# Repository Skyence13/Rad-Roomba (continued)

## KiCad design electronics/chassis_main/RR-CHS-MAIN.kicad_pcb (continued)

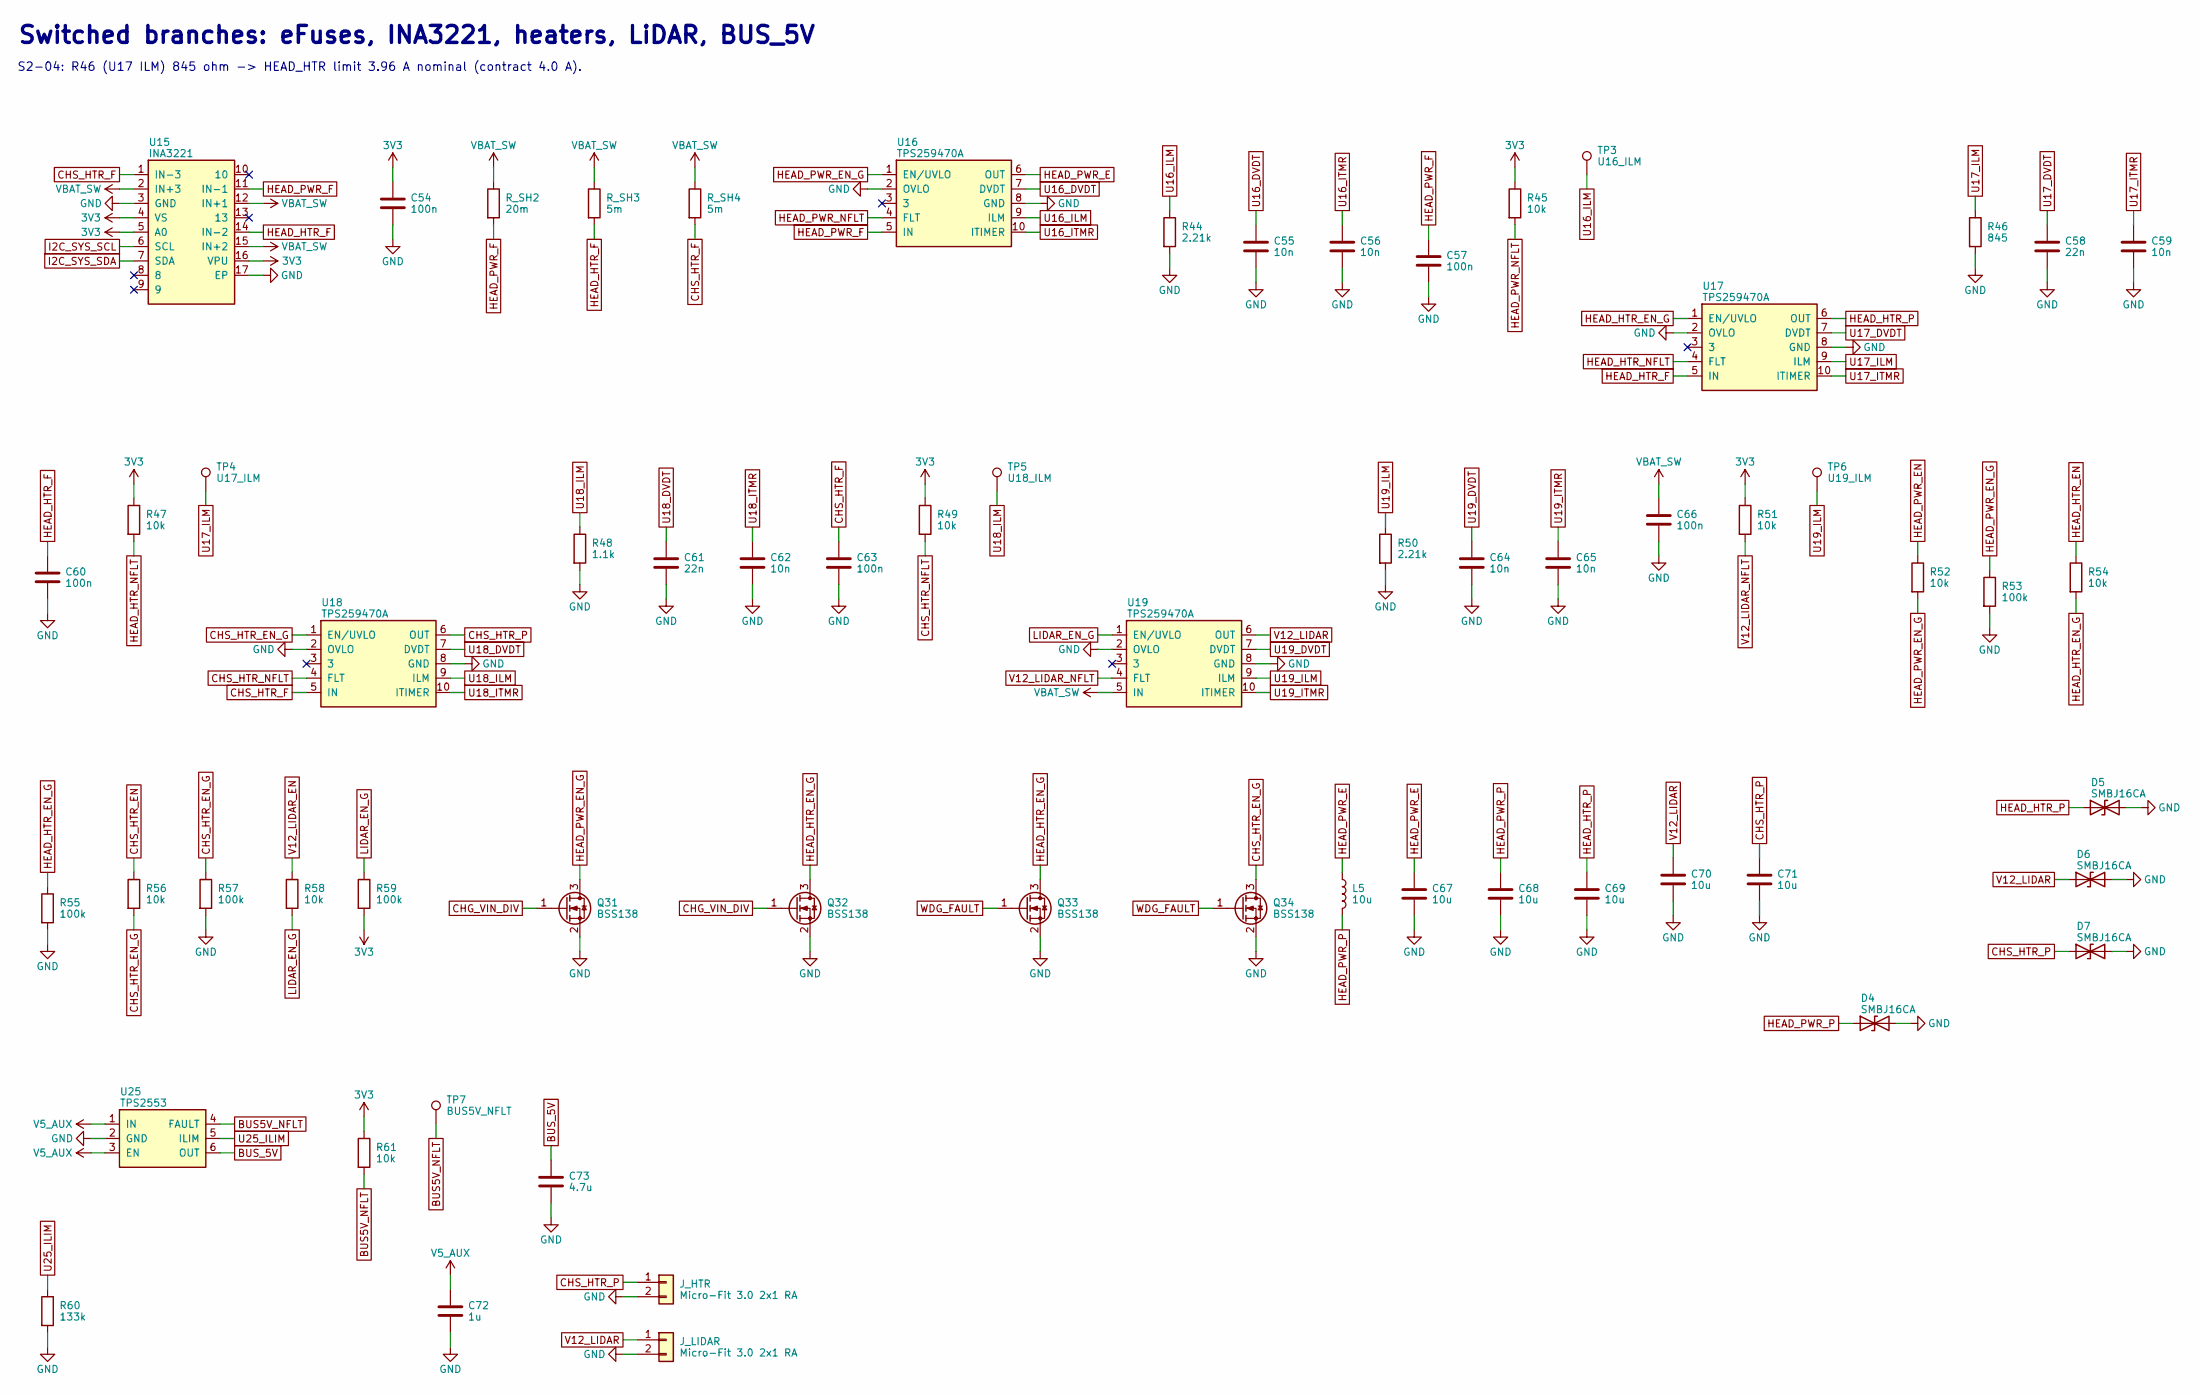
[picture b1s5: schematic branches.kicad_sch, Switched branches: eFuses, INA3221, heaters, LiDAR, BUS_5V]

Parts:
C54, C57, C60, C63, C66: 100n; C_0603_1608Metric; MPN CC0603KRX7R9BB104
C55, C56, C59, C62, C64, C65: 10n; C_0603_1608Metric; MPN CC0603KRX7R9BB103
C58, C61: 22n; C_0603_1608Metric; MPN CC0603KRX7R9BB223
C67, C68, C69, C70, C71: 10u; C_1206_3216Metric; MPN GRM31CR71E106KA12L
C72: 1u; C_0603_1608Metric; MPN GRM188R71C105KA12D
C73: 4.7u; C_0805_2012Metric; MPN GRM21BR71C475KA73L
D4, D5, D6, D7: SMBJ16CA; D_SMB; MPN SMBJ16CA
J_HTR: Micro-Fit 3.0 2x1 RA; Molex_Micro-Fit_3.0_43045-0200_2x01_P3.00mm_Horizontal; MPN 43045-0200
J_LIDAR: Micro-Fit 3.0 2x1 RA; Molex_Micro-Fit_3.0_43045-0200_2x01_P3.00mm_Horizontal; MPN 43045-0200
L5: 10u; L_Coilcraft_XAL4040-XXX; MPN XAL4040-103MEC
Q31, Q32, Q33, Q34: BSS138; SOT-23; MPN BSS138
R44, R50: 2.21k; R_0603_1608Metric; MPN RC0603FR-072K21L
R45, R47, R49, R51, R52, R54, R56, R58, R61: 10k; R_0603_1608Metric; MPN RC0603FR-0710KL
R46: 845; R_0603_1608Metric; MPN RC0603FR-07845RL
R48: 1.1k; R_0603_1608Metric; MPN RC0603FR-071K1L
R53, R55, R57, R59: 100k; R_0603_1608Metric; MPN RC0603FR-07100KL
R60: 133k; R_0603_1608Metric; MPN RC0603FR-07133KL
R_SH2: 20m; R_1206_3216Metric; MPN WSL1206R0200FEA
R_SH3, R_SH4: 5m; R_2512_6332Metric; MPN WSL25125L000FEA
TP3: U16_ILM; TestPoint_Keystone_5019_Miniature; MPN 5019
TP4: U17_ILM; TestPoint_Keystone_5019_Miniature; MPN 5019
TP5: U18_ILM; TestPoint_Keystone_5019_Miniature; MPN 5019
TP6: U19_ILM; TestPoint_Keystone_5019_Miniature; MPN 5019
TP7: BUS5V_NFLT; TestPoint_Keystone_5019_Miniature; MPN 5019
U15: INA3221; Texas_RGV0016A_VQFN-16-1EP_4x4mm_P0.65mm_EP2.1x2.1mm; MPN INA3221AIRGVR
U16, U17, U18, U19: TPS259470A; TI_RPW0010A_VQFN-HR-10_2x2mm_PLACEHOLDER; MPN TPS259470ARPWR
U25: TPS2553; SOT-23-6; MPN TPS2553DBVR

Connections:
3V3: C54.1, R45.1, R47.1, R49.1, R51.1, R59.2, R61.1, U15.4 (VS), U15.5 (A0), U15.16 (VPU); also elsewhere on the board
BUS5V_NFLT: R61.2, TP7.1, U25.4 (FAULT)
BUS_5V: C73.1, U25.6 (OUT); also elsewhere on the board
CHG_VIN_DIV: Q31.1 (G), Q32.1 (G); also elsewhere on the board
CHS_HTR_EN: R56.1; also elsewhere on the board
CHS_HTR_EN_G: Q34.3 (D), R56.2, R57.1, U18.1 (EN/UVLO)
CHS_HTR_F: C63.1, R_SH4.2, U15.1 (IN-3), U18.5 (IN)
CHS_HTR_NFLT: R49.2, U18.4 (FLT); also elsewhere on the board
CHS_HTR_P: C71.1, D7.1 (A1), J_HTR.1, U18.6 (OUT)
GND: C54.2, C55.2, C56.2, C57.2, C58.2, C59.2, C60.2, C61.2, C62.2, C63.2, C64.2, C65.2, C66.2, C67.2, C68.2, C69.2, C70.2, C71.2, C72.2, C73.2, D4.2 (A2), D5.2 (A2), D6.2 (A2), D7.2 (A2), J_HTR.2, J_LIDAR.2, Q31.2 (S), Q32.2 (S), Q33.2 (S), Q34.2 (S), R44.2, R46.2, R48.2, R50.2, R53.2, R55.2, R57.2, R60.2, U15.3 (GND), U15.17 (EP), U16.2 (OVLO), U16.8 (GND), U17.2 (OVLO), U17.8 (GND), U18.2 (OVLO), U18.8 (GND), U19.2 (OVLO), U19.8 (GND), U25.2 (GND); also elsewhere on the board
HEAD_HTR_EN: R54.1; also elsewhere on the board
HEAD_HTR_EN_G: Q32.3 (D), Q33.3 (D), R54.2, R55.1, U17.1 (EN/UVLO)
HEAD_HTR_F: C60.1, R_SH3.2, U15.14 (IN-2), U17.5 (IN)
HEAD_HTR_NFLT: R47.2, U17.4 (FLT); also elsewhere on the board
HEAD_HTR_P: C69.1, D5.1 (A1), U17.6 (OUT); also elsewhere on the board
HEAD_PWR_E: C67.1, L5.1, U16.6 (OUT)
HEAD_PWR_EN: R52.1; also elsewhere on the board
HEAD_PWR_EN_G: Q31.3 (D), R52.2, R53.1, U16.1 (EN/UVLO)
HEAD_PWR_F: C57.1, R_SH2.2, U15.11 (IN-1), U16.5 (IN)
HEAD_PWR_NFLT: R45.2, U16.4 (FLT); also elsewhere on the board
HEAD_PWR_P: C68.1, D4.1 (A1), L5.2; also elsewhere on the board
I2C_SYS_SCL: U15.6 (SCL); also elsewhere on the board
I2C_SYS_SDA: U15.7 (SDA); also elsewhere on the board
LIDAR_EN_G: R58.2, R59.1, U19.1 (EN/UVLO)
U16_DVDT: C55.1, U16.7 (DVDT)
U16_ILM: R44.1, TP3.1, U16.9 (ILM)
U16_ITMR: C56.1, U16.10 (ITIMER)
U17_DVDT: C58.1, U17.7 (DVDT)
U17_ILM: R46.1, TP4.1, U17.9 (ILM)
U17_ITMR: C59.1, U17.10 (ITIMER)
U18_DVDT: C61.1, U18.7 (DVDT)
U18_ILM: R48.1, TP5.1, U18.9 (ILM)
U18_ITMR: C62.1, U18.10 (ITIMER)
U19_DVDT: C64.1, U19.7 (DVDT)
U19_ILM: R50.1, TP6.1, U19.9 (ILM)
U19_ITMR: C65.1, U19.10 (ITIMER)
U25_ILIM: R60.1, U25.5 (ILIM)
V5_AUX: C72.1, U25.1 (IN), U25.3 (EN); also elsewhere on the board
V12_LIDAR: C70.1, D6.1 (A1), J_LIDAR.1, U19.6 (OUT)
V12_LIDAR_EN: R58.1; also elsewhere on the board
V12_LIDAR_NFLT: R51.2, U19.4 (FLT); also elsewhere on the board
VBAT_SW: C66.1, R_SH2.1, R_SH3.1, R_SH4.1, U15.2 (IN+3), U15.12 (IN+1), U15.15 (IN+2), U19.5 (IN); also elsewhere on the board
WDG_FAULT: Q33.1 (G), Q34.1 (G); also elsewhere on the board

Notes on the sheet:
Switched branches: eFuses, INA3221, heaters, LiDAR, BUS_5V
S2-04: R46 (U17 ILM) 845 ohm -> HEAD_HTR limit 3.96 A nominal (contract 4.0 A).

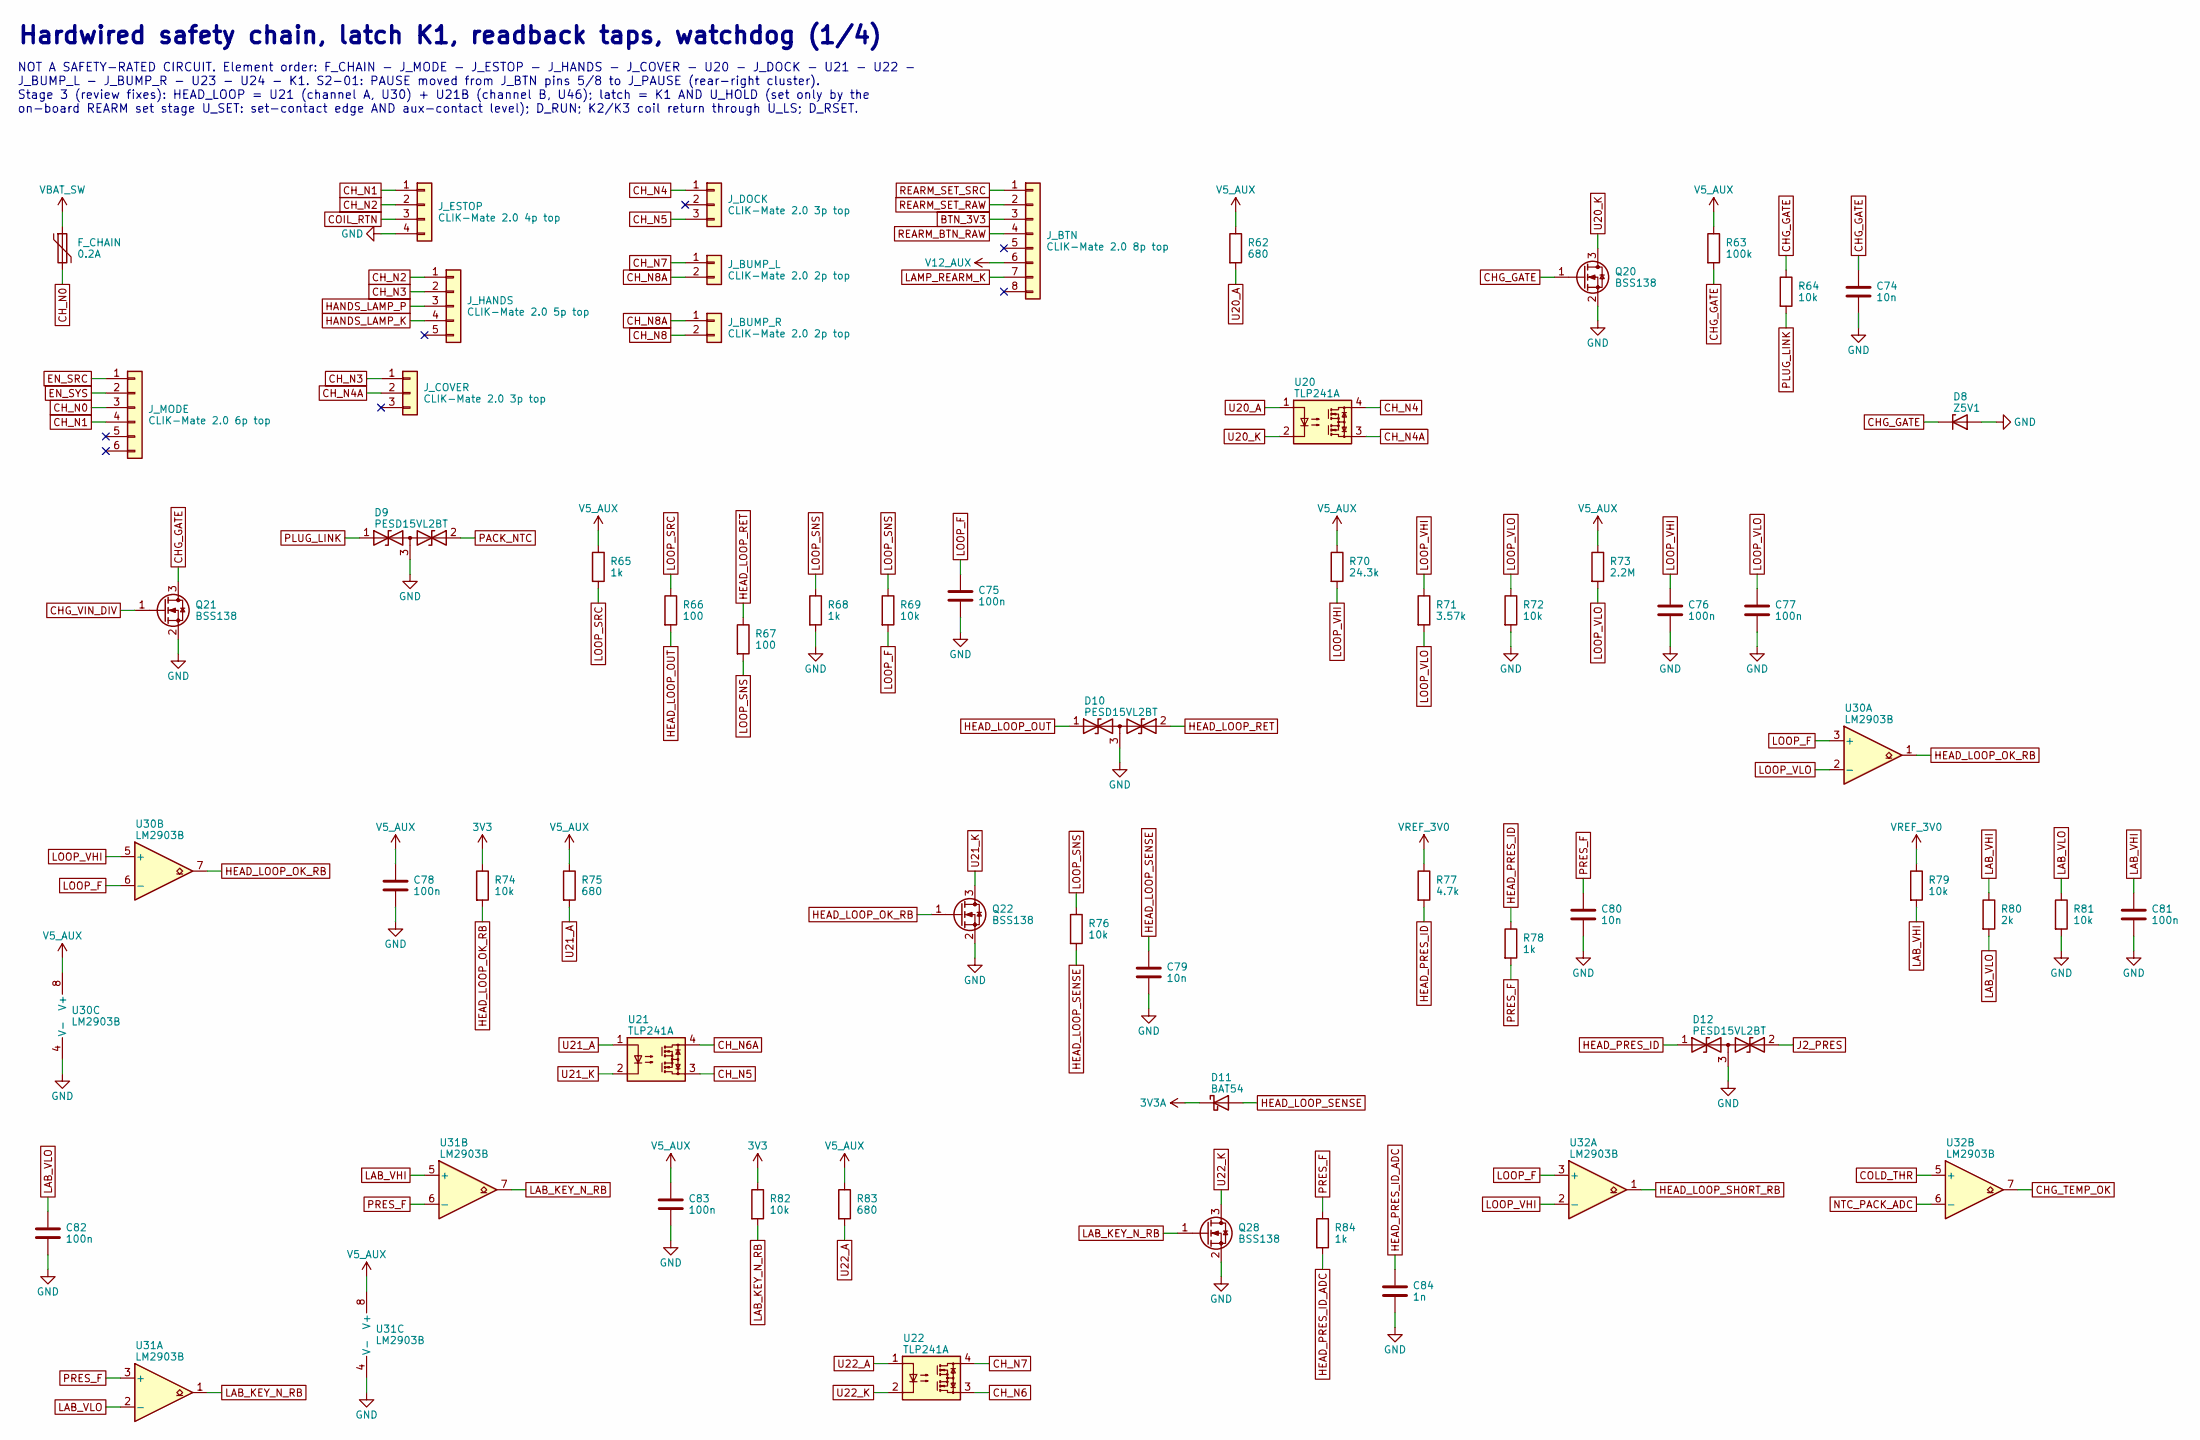
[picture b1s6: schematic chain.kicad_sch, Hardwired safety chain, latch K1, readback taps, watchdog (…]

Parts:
C74, C79, C80: 10n; C_0603_1608Metric; MPN CC0603KRX7R9BB103
C75, C76, C77, C78, C81, C82, C83: 100n; C_0603_1608Metric; MPN CC0603KRX7R9BB104
C84: 1n; C_0603_1608Metric; MPN CC0603JRNPO9BN102
D8: Z5V1; D_SOD-123; MPN BZT52C5V1-7-F
D9, D10, D12: PESD15VL2BT; SOT-23; MPN PESD15VL2BT,215
D11: BAT54; D_SOD-123; MPN BAT54W-7-F
F_CHAIN: 0.2A; Fuse_1206_3216Metric; MPN 1206L020YR
J_BTN: CLIK-Mate 2.0 8p top; Molex_CLIK-Mate_502443-0870_1x08-1MP_P2.00mm_Vertical; MPN 502443-0870
J_BUMP_L: CLIK-Mate 2.0 2p top; Molex_CLIK-Mate_502443-0270_1x02-1MP_P2.00mm_Vertical; MPN 502443-0270
J_BUMP_R: CLIK-Mate 2.0 2p top; Molex_CLIK-Mate_502443-0270_1x02-1MP_P2.00mm_Vertical; MPN 502443-0270
J_COVER: CLIK-Mate 2.0 3p top; Molex_CLIK-Mate_502443-0370_1x03-1MP_P2.00mm_Vertical; MPN 502443-0370
J_DOCK: CLIK-Mate 2.0 3p top; Molex_CLIK-Mate_502443-0370_1x03-1MP_P2.00mm_Vertical; MPN 502443-0370
J_ESTOP: CLIK-Mate 2.0 4p top; Molex_CLIK-Mate_502443-0470_1x04-1MP_P2.00mm_Vertical; MPN 502443-0470
J_HANDS: CLIK-Mate 2.0 5p top; Molex_CLIK-Mate_502443-0570_1x05-1MP_P2.00mm_Vertical; MPN 502443-0570
J_MODE: CLIK-Mate 2.0 6p top; Molex_CLIK-Mate_502443-0670_1x06-1MP_P2.00mm_Vertical; MPN 502443-0670
Q20, Q21, Q22, Q28: BSS138; SOT-23; MPN BSS138
R62, R75, R83: 680; R_0603_1608Metric; MPN RC0603FR-07680RL
R63: 100k; R_0603_1608Metric; MPN RC0603FR-07100KL
R64, R69, R74, R76, R82: 10k; R_0603_1608Metric; MPN RC0603FR-0710KL
R65, R68: 1k; R_0603_1608Metric; MPN RT0603BRD071KL
R66, R67: 100; R_0603_1608Metric; MPN RC0603FR-07100RL
R70: 24.3k; R_0603_1608Metric; MPN RT0603BRD0724K3L
R71: 3.57k; R_0603_1608Metric; MPN RT0603BRD073K57L
R72, R79, R81: 10k; R_0603_1608Metric; MPN RT0603BRD0710KL
R73: 2.2M; R_0603_1608Metric; MPN RC0603FR-072M2L
R77: 4.7k; R_0603_1608Metric; MPN RT0603BRD074K7L
R78, R84: 1k; R_0603_1608Metric; MPN RC0603FR-071KL
R80: 2k; R_0603_1608Metric; MPN RT0603BRD072KL
U20, U21, U22: TLP241A; SMDIP-4_W9.53mm; MPN TLP241A(TP1,F
U30, U31, U32: LM2903B; SOIC-8_3.9x4.9mm_P1.27mm; MPN LM2903BIDR

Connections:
3V3: R74.1, R82.1; also elsewhere on the board
3V3A: D11.1 (K); also elsewhere on the board
BTN_3V3: J_BTN.3; also elsewhere on the board
CHG_GATE: C74.1, D8.1 (K), Q20.1 (G), Q21.3 (D), R63.2, R64.1
CHG_TEMP_OK: U32.7; also elsewhere on the board
CHG_VIN_DIV: Q21.1 (G); also elsewhere on the board
CH_N0: F_CHAIN.2, J_MODE.3; also elsewhere on the board
CH_N1: J_ESTOP.1, J_MODE.4; also elsewhere on the board
CH_N2: J_ESTOP.2, J_HANDS.1; also elsewhere on the board
CH_N3: J_COVER.1, J_HANDS.2; also elsewhere on the board
CH_N4: J_DOCK.1, U20.4; also elsewhere on the board
CH_N4A: J_COVER.2, U20.3; also elsewhere on the board
CH_N5: J_DOCK.3, U21.3; also elsewhere on the board
CH_N6: U22.3; also elsewhere on the board
CH_N6A: U21.4; also elsewhere on the board
CH_N7: J_BUMP_L.1, U22.4; also elsewhere on the board
CH_N8: J_BUMP_R.2; also elsewhere on the board
CH_N8A: J_BUMP_L.2, J_BUMP_R.1; also elsewhere on the board
COIL_RTN: J_ESTOP.3; also elsewhere on the board
COLD_THR: U32.5 (+); also elsewhere on the board
EN_SRC: J_MODE.1; also elsewhere on the board
EN_SYS: J_MODE.2; also elsewhere on the board
GND: C74.2, C75.2, C76.2, C77.2, C78.2, C79.2, C80.2, C81.2, C82.2, C83.2, C84.2, D8.2 (A), D9.3 (common), D10.3 (common), D12.3 (common), J_ESTOP.4, Q20.2 (S), Q21.2 (S), Q22.2 (S), Q28.2 (S), R68.2, R72.2, R81.2, U30.4 (V-), U31.4 (V-); also elsewhere on the board
HANDS_LAMP_K: J_HANDS.4; also elsewhere on the board
HANDS_LAMP_P: J_HANDS.3; also elsewhere on the board
HEAD_LOOP_OK_RB: Q22.1 (G), R74.2, U30.1, U30.7; also elsewhere on the board
HEAD_LOOP_OUT: D10.1 (A1), R66.2; also elsewhere on the board
HEAD_LOOP_RET: D10.2 (A2), R67.1; also elsewhere on the board
HEAD_LOOP_SENSE: C79.1, D11.2 (A), R76.2; also elsewhere on the board
HEAD_LOOP_SHORT_RB: U32.1; also elsewhere on the board
HEAD_PRES_ID: D12.1 (A1), R77.2, R78.1; also elsewhere on the board
HEAD_PRES_ID_ADC: C84.1, R84.2; also elsewhere on the board
J2_PRES: D12.2 (A2); also elsewhere on the board
LAB_KEY_N_RB: Q28.1 (G), R82.2, U31.1, U31.7; also elsewhere on the board
LAB_VHI: C81.1, R79.2, R80.1, U31.5 (+)
LAB_VLO: C82.1, R80.2, R81.1, U31.2 (-)
LAMP_REARM_K: J_BTN.7; also elsewhere on the board
LOOP_F: C75.1, R69.2, U30.3 (+), U30.6 (-), U32.3 (+); also elsewhere on the board
LOOP_SNS: R67.2, R68.1, R69.1, R76.1; also elsewhere on the board
LOOP_SRC: R65.2, R66.1
LOOP_VHI: C76.1, R70.2, R71.1, U30.5 (+), U32.2 (-)
LOOP_VLO: C77.1, R71.2, R72.1, R73.2, U30.2 (-)
NTC_PACK_ADC: U32.6 (-); also elsewhere on the board
PACK_NTC: D9.2 (A2); also elsewhere on the board
PLUG_LINK: D9.1 (A1), R64.2; also elsewhere on the board
PRES_F: C80.1, R78.2, R84.1, U31.3 (+), U31.6 (-); also elsewhere on the board
REARM_BTN_RAW: J_BTN.4; also elsewhere on the board
REARM_SET_RAW: J_BTN.2; also elsewhere on the board
REARM_SET_SRC: J_BTN.1; also elsewhere on the board
U20_A: R62.2, U20.1
U20_K: Q20.3 (D), U20.2
U21_A: R75.2, U21.1
U21_K: Q22.3 (D), U21.2
U22_A: R83.2, U22.1
U22_K: Q28.3 (D), U22.2
V5_AUX: C78.1, C83.1, R62.1, R63.1, R65.1, R70.1, R73.1, R75.1, R83.1, U30.8 (V+), U31.8 (V+); also elsewhere on the board
V12_AUX: J_BTN.6; also elsewhere on the board
VBAT_SW: F_CHAIN.1; also elsewhere on the board
VREF_3V0: R77.1, R79.1; also elsewhere on the board

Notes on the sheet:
Hardwired safety chain, latch K1, readback taps, watchdog (1/4)
NOT A SAFETY-RATED CIRCUIT. Element order: F_CHAIN - J_MODE - J_ESTOP - J_HANDS - J_COVER - U20 - J_DOCK - U21 - U22 - J_BUMP_L - J_BUMP_R - U23 - U24 - K1. S2-01: PAUSE moved from J_BTN pins 5/8 to J_PAUSE (rear-right cluster). Stage 3 (review fixes): HEAD_LOOP = U21 (channel A, U30) + U21B (chann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

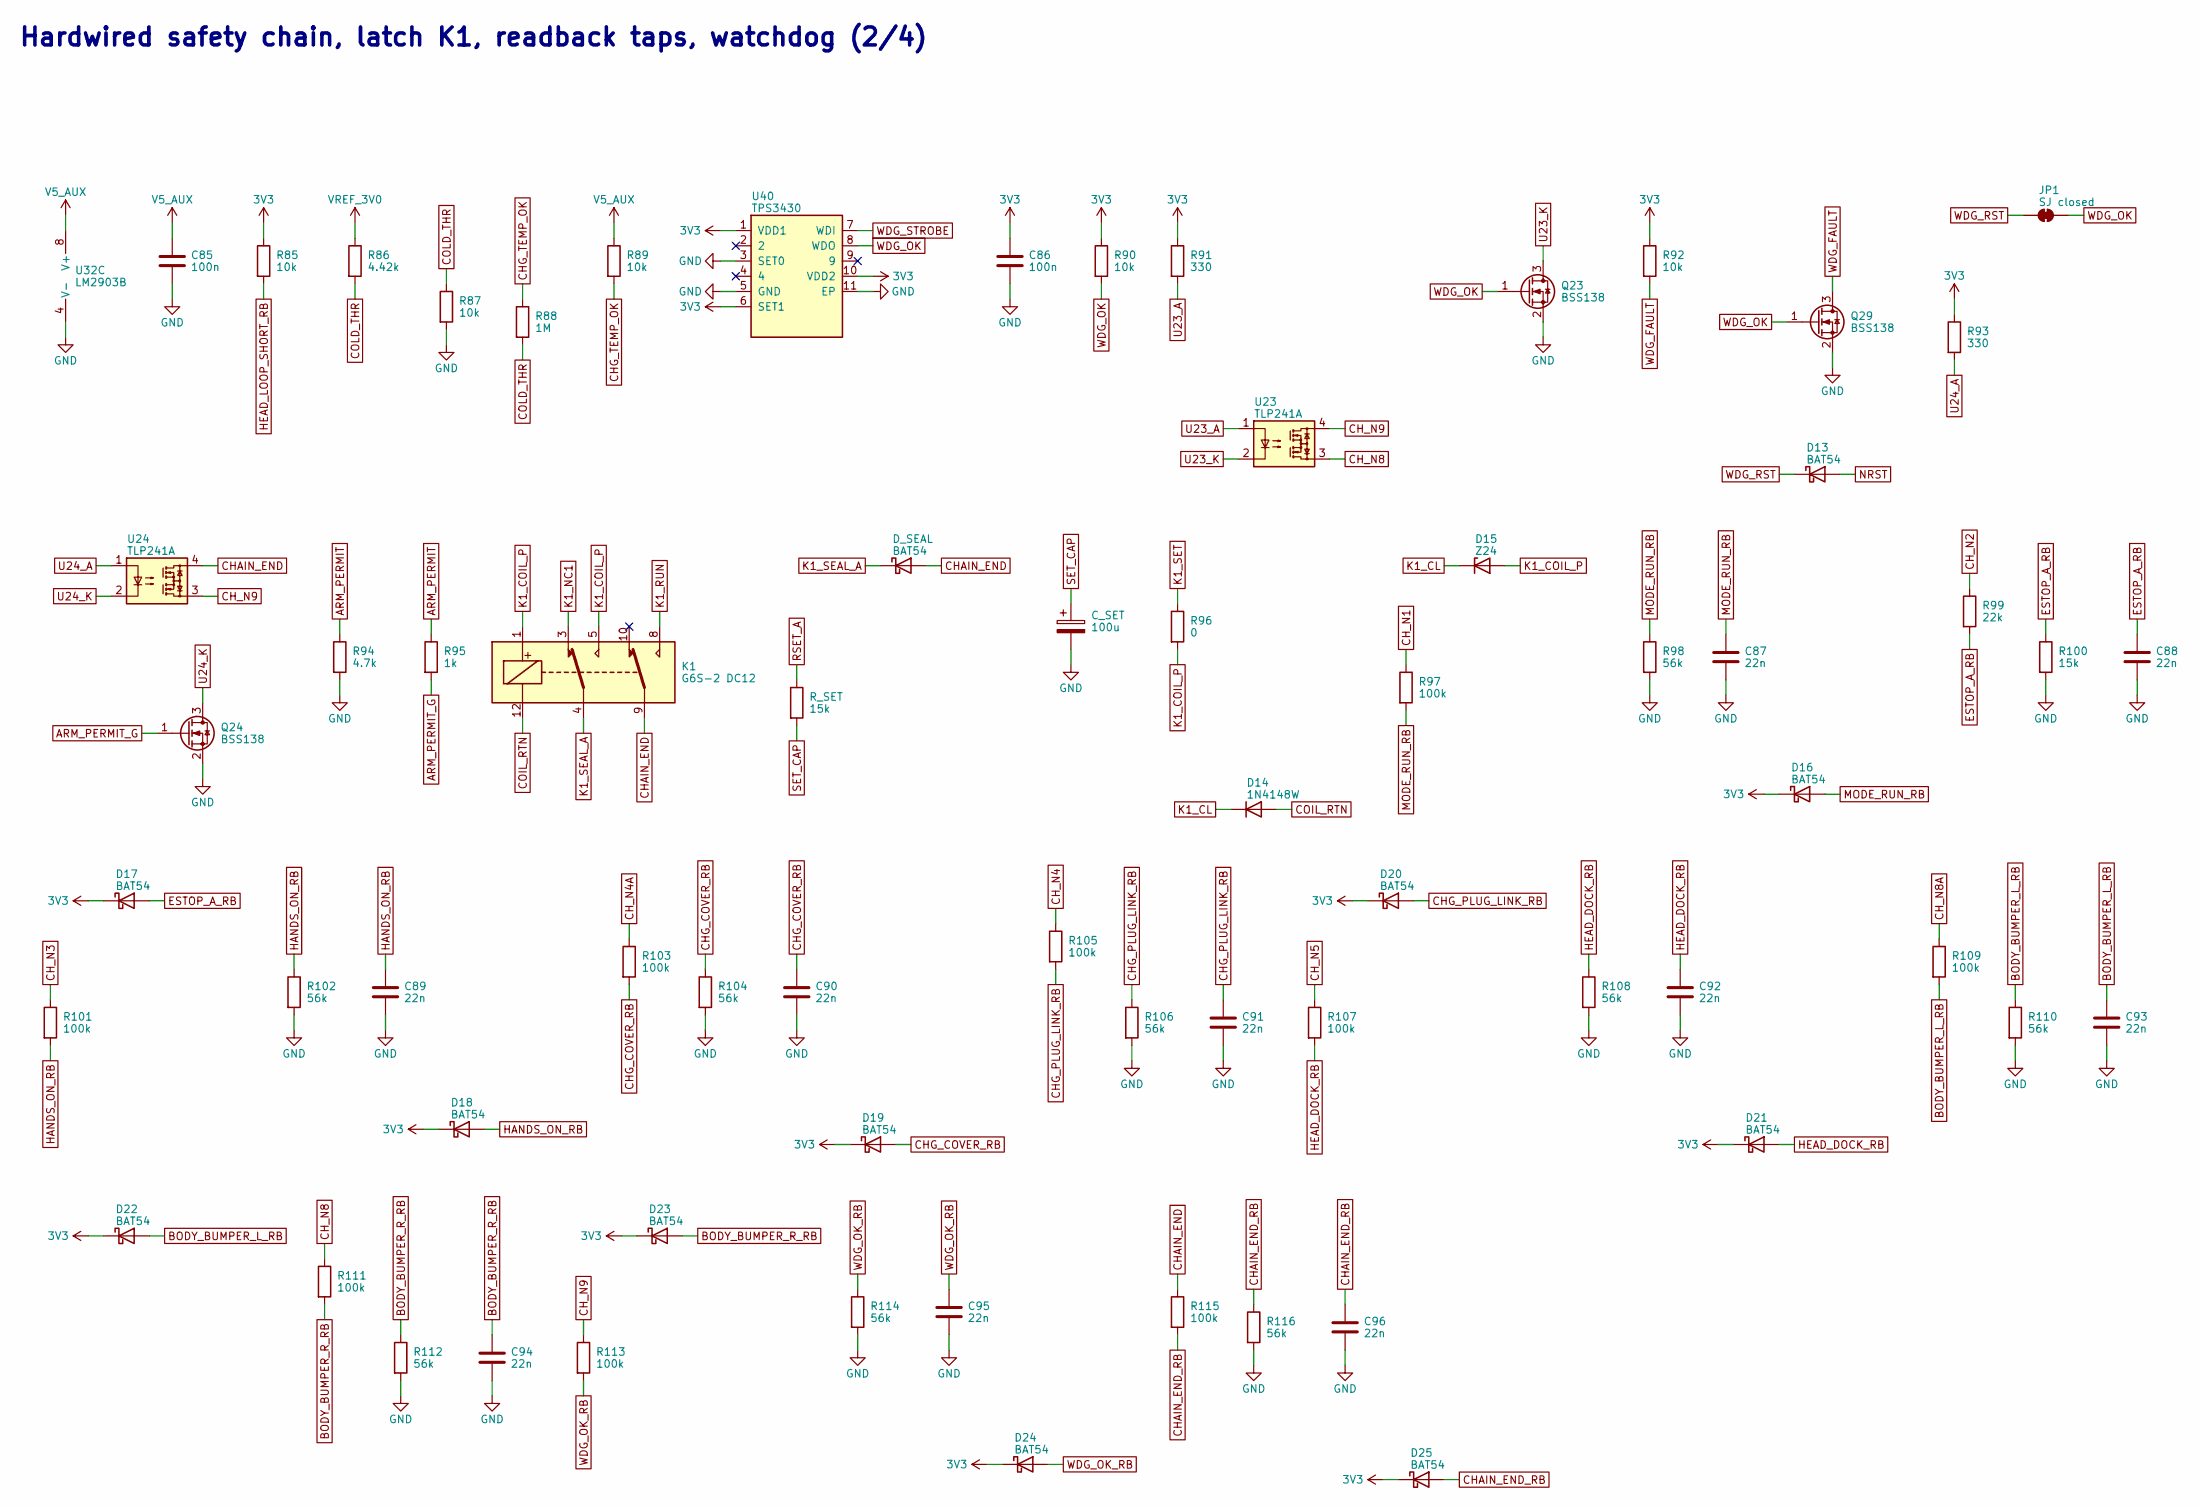
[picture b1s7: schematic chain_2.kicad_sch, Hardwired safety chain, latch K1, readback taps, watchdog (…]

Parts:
C85, C86: 100n; C_0603_1608Metric; MPN CC0603KRX7R9BB104
C87, C88, C89, C90, C91, C92, C93, C94, C95, C96: 22n; C_0603_1608Metric; MPN CC0603KRX7R9BB223
C_SET: 100u; CP_Elec_10x10.5; MPN EEHZA1H101P
D13, D16, D17, D18, D19, D20, D21, D22, D23, D24, D25: BAT54; D_SOD-123; MPN BAT54W-7-F
D14: 1N4148W; D_SOD-123; MPN 1N4148W-7-F
D15: Z24; D_SOD-123; MPN BZT52C24-7-F
D_SEAL: BAT54; D_SOD-123; MPN BAT54W-7-F
JP1: SJ closed; SolderJumper-2_P1.3mm_Bridged_RoundedPad1.0x1.5mm; MPN SOLDER-JUMPER
K1: G6S-2 DC12; Relay_DPDT_Omron_G6S-2; MPN G6S-2 DC12
Q23, Q24, Q29: BSS138; SOT-23; MPN BSS138
R85, R87, R89, R90, R92: 10k; R_0603_1608Metric; MPN RC0603FR-0710KL
R86: 4.42k; R_0603_1608Metric; MPN RC0603FR-074K42L
R88: 1M; R_0603_1608Metric; MPN RC0603FR-071ML
R91, R93: 330; R_0603_1608Metric; MPN RC0603FR-07330RL
R94: 4.7k; R_0603_1608Metric; MPN RC0603FR-074K7L
R95: 1k; R_0603_1608Metric; MPN RC0603FR-071KL
R96: 0; R_0603_1608Metric; MPN RC0603FR-070RL
R97, R101, R103, R105, R107, R109, R111, R113, R115: 100k; R_0603_1608Metric; MPN RC0603FR-07100KL
R98, R102, R104, R106, R108, R110, R112, R114, R116: 56k; R_0603_1608Metric; MPN RC0603FR-0756KL
R99: 22k; R_0603_1608Metric; MPN RC0603FR-0722KL
R100: 15k; R_0603_1608Metric; MPN RC0603FR-0715KL
R_SET: 15k; R_0603_1608Metric; MPN RC0603FR-0715KL
U23, U24: TLP241A; SMDIP-4_W9.53mm; MPN TLP241A(TP1,F
U32: LM2903B; SOIC-8_3.9x4.9mm_P1.27mm; MPN LM2903BIDR
U40: TPS3430; VSON-10-1EP_3x3mm_P0.5mm_EP1.65x2.4mm; MPN TPS3430WDRCR

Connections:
3V3: C86.1, D16.1 (K), D17.1 (K), D18.1 (K), D19.1 (K), D20.1 (K), D21.1 (K), D22.1 (K), D23.1 (K), D24.1 (K), D25.1 (K), R85.1, R90.1, R91.1, R92.1, R93.1, U40.1 (VDD1), U40.6 (SET1), U40.10 (VDD2); also elsewhere on the board
ARM_PERMIT: R94.1, R95.1; also elsewhere on the board
ARM_PERMIT_G: Q24.1 (G), R95.2
BODY_BUMPER_L_RB: C93.1, D22.2 (A), R109.2, R110.1; also elsewhere on the board
BODY_BUMPER_R_RB: C94.1, D23.2 (A), R111.2, R112.1; also elsewhere on the board
CHAIN_END: D_SEAL.2 (A), K1.9, R115.1, U24.4; also elsewhere on the board
CHAIN_END_RB: C96.1, D25.2 (A), R115.2, R116.1; also elsewhere on the board
CHG_COVER_RB: C90.1, D19.2 (A), R103.2, R104.1; also elsewhere on the board
CHG_PLUG_LINK_RB: C91.1, D20.2 (A), R105.2, R106.1; also elsewhere on the board
CHG_TEMP_OK: R88.1, R89.2; also elsewhere on the board
CH_N1: R97.1; also elsewhere on the board
CH_N2: R99.1; also elsewhere on the board
CH_N3: R101.1; also elsewhere on the board
CH_N4: R105.1; also elsewhere on the board
CH_N4A: R103.1; also elsewhere on the board
CH_N5: R107.1; also elsewhere on the board
CH_N8: R111.1, U23.3; also elsewhere on the board
CH_N8A: R109.1; also elsewhere on the board
CH_N9: R113.1, U23.4, U24.3
COIL_RTN: D14.2 (A), K1.12; also elsewhere on the board
COLD_THR: R86.2, R87.1, R88.2; also elsewhere on the board
ESTOP_A_RB: C88.1, D17.2 (A), R99.2, R100.1; also elsewhere on the board
GND: C85.2, C86.2, C87.2, C88.2, C89.2, C90.2, C91.2, C92.2, C93.2, C94.2, C95.2, C96.2, C_SET.2, Q23.2 (S), Q24.2 (S), Q29.2 (S), R87.2, R94.2, R98.2, R100.2, R102.2, R104.2, R106.2, R108.2, R110.2, R112.2, R114.2, R116.2, U32.4 (V-), U40.3 (SET0), U40.5 (GND), U40.11 (EP); also elsewhere on the board
HANDS_ON_RB: C89.1, D18.2 (A), R101.2, R102.1; also elsewhere on the board
HEAD_DOCK_RB: C92.1, D21.2 (A), R107.2, R108.1; also elsewhere on the board
HEAD_LOOP_SHORT_RB: R85.2; also elsewhere on the board
K1_CL: D14.1 (K), D15.1 (K)
K1_COIL_P: D15.2 (A), K1.1, K1.5, R96.2
K1_NC1: K1.3; also elsewhere on the board
K1_RUN: K1.8; also elsewhere on the board
K1_SEAL_A: D_SEAL.1 (K), K1.4; also elsewhere on the board
K1_SET: R96.1; also elsewhere on the board
MODE_RUN_RB: C87.1, D16.2 (A), R97.2, R98.1; also elsewhere on the board
NRST: D13.2 (A); also elsewhere on the board
RSET_A: R_SET.1; also elsewhere on the board
SET_CAP: C_SET.1, R_SET.2; also elsewhere on the board
U23_A: R91.2, U23.1
U23_K: Q23.3 (D), U23.2
U24_A: R93.2, U24.1
U24_K: Q24.3 (D), U24.2
V5_AUX: C85.1, R89.1, U32.8 (V+); also elsewhere on the board
VREF_3V0: R86.1; also elsewhere on the board
WDG_FAULT: Q29.3 (D), R92.2; also elsewhere on the board
WDG_OK: JP1.2 (B), Q23.1 (G), Q29.1 (G), R90.2, U40.8 (WDO); also elsewhere on the board
WDG_OK_RB: C95.1, D24.2 (A), R113.2, R114.1; also elsewhere on the board
WDG_RST: D13.1 (K), JP1.1 (A)
WDG_STROBE: U40.7 (WDI); also elsewhere on the board

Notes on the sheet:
Hardwired safety chain, latch K1, readback taps, watchdog (2/4)
